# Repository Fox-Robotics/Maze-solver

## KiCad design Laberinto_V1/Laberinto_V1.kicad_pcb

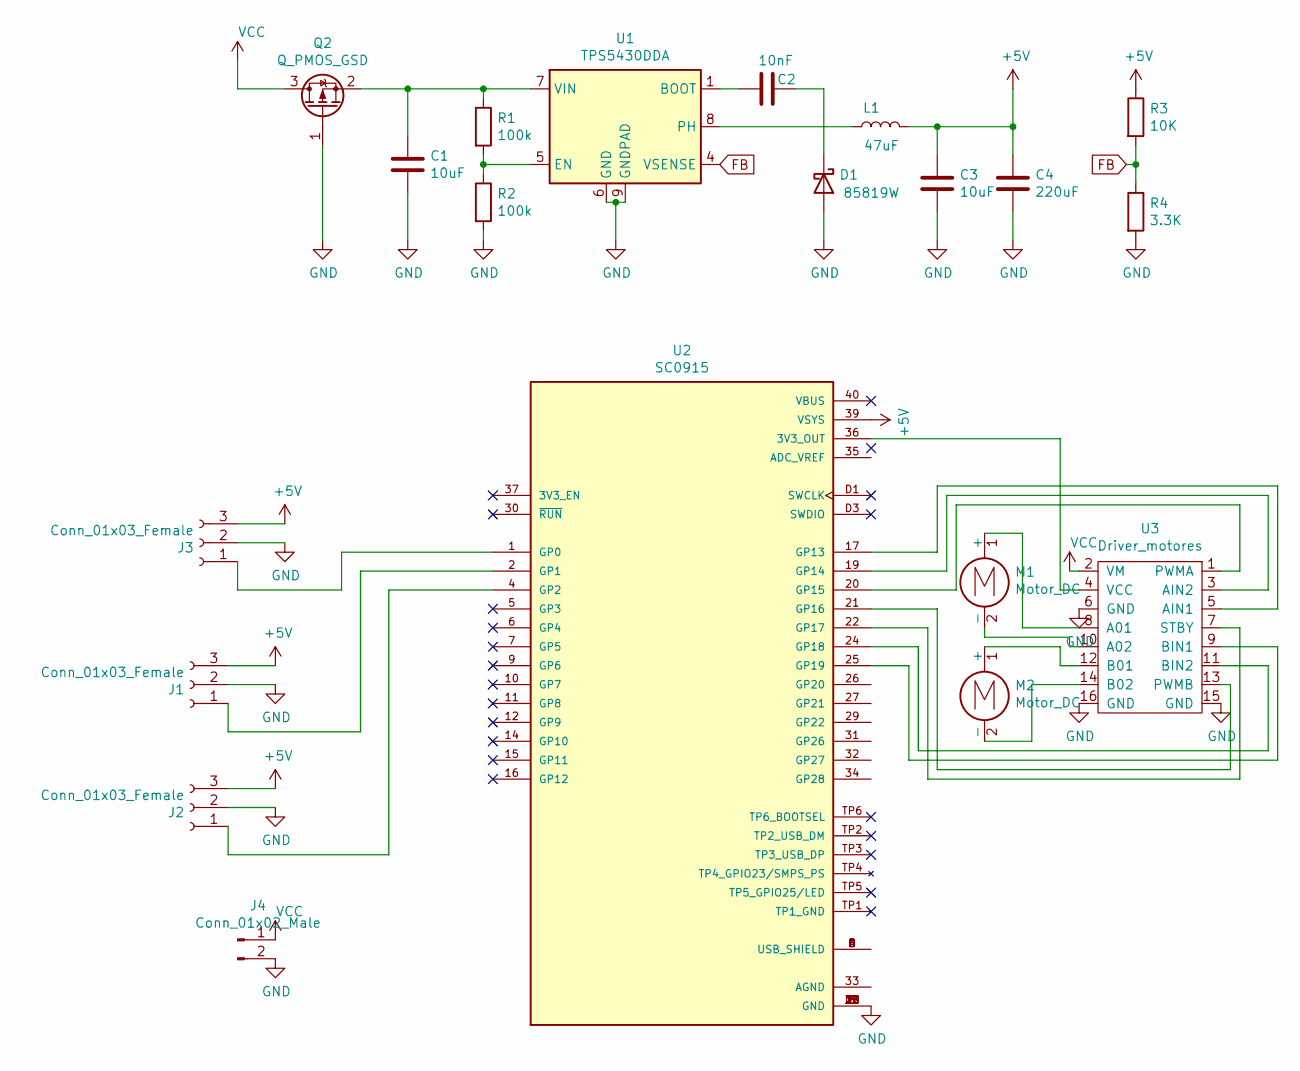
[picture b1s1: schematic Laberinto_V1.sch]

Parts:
C1: 10uF; CP_Elec_5x5.9
C2: 10nF; C_0805_2012Metric_Pad1.18x1.45mm_HandSolder
C3: 10uF; C_0805_2012Metric_Pad1.18x1.45mm_HandSolder
C4: 220uF; CAP_10TPB220M
D1: 85819W; D_SOD-123F
J1, J2, J3: Conn_01x03_Female; PinSocket_1x03_P2.54mm_Horizontal
J4: Conn_01x02_Male; PinHeader_1x02_P2.54mm_Vertical
L1: 47uF; L_0805_2012Metric_Pad1.15x1.40mm_HandSolder
M1, M2: Motor_DC; PinHeader_1x02_P2.54mm_Vertical
Q2: Q_PMOS_GSD; SOT23
R1, R2: 100k; R_0805_2012Metric_Pad1.20x1.40mm_HandSolder
R3: 10K; R_0805_2012Metric_Pad1.20x1.40mm_HandSolder
R4: 3.3K; R_0805_2012Metric_Pad1.20x1.40mm_HandSolder
U1: TPS5430DDA; TI_SO-PowerPAD-8_ThermalVias
U2: SC0915; MODULE_SC0915; PARTREV 1.6
U3: Driver_motores; Motor_driver

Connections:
+5V: C3.1, C4.1, J1.3, J2.3, J3.3, L1.2, R3.1, U2.39 (VSYS)
FB: R3.2, R4.1, U1.4 (VSENSE)
GND: C1.2, C3.2, C4.2, D1.2 (A), J1.2, J2.2, J3.2, J4.2, Q2.1 (G), R2.2, R4.2, U1.6 (GND), U1.9 (GNDPAD), U2.3 (GND), U2.8 (GND), U2.13 (GND), U2.18 (GND), U2.23 (GND), U2.28 (GND), U2.38 (GND), U2.D2 (GND), U3.6 (GND), U3.15 (GND), U3.16 (GND)
unnamed: C1.1, Q2.2 (S), R1.1, U1.7 (VIN)
unnamed: C2.1, D1.1 (K)
unnamed: C2.2, U1.1 (BOOT)
unnamed: J1.1, U2.2 (GP1)
unnamed: J2.1, U2.4 (GP2)
unnamed: J3.1, U2.1 (GP0)
unnamed: L1.1, U1.8 (PH)
unnamed: M1.1 (+), U3.8 (A01)
unnamed: M1.2 (-), U3.10 (A02)
unnamed: M2.1 (+), U3.12 (B01)
unnamed: M2.2 (-), U3.14 (B02)
unnamed: R1.2, R2.1, U1.5 (EN)
unnamed: U2.17 (GP13), U3.5 (AIN1)
unnamed: U2.19 (GP14), U3.3 (AIN2)
unnamed: U2.20 (GP15), U3.1 (PWMA)
unnamed: U2.21 (GP16), U3.13 (PWMB)
unnamed: U2.22 (GP17), U3.7 (STBY)
unnamed: U2.24 (GP18), U3.11 (BIN2)
unnamed: U2.25 (GP19), U3.9 (BIN1)
unnamed: U2.36 (3V3_OUT), U3.4 (VCC)
unnamed: U2.A (USB_SHIELD), U2.B (USB_SHIELD), U2.C (USB_SHIELD), U2.D (USB_SHIELD)
VCC: J4.1, Q2.3 (D), U3.2 (VM)

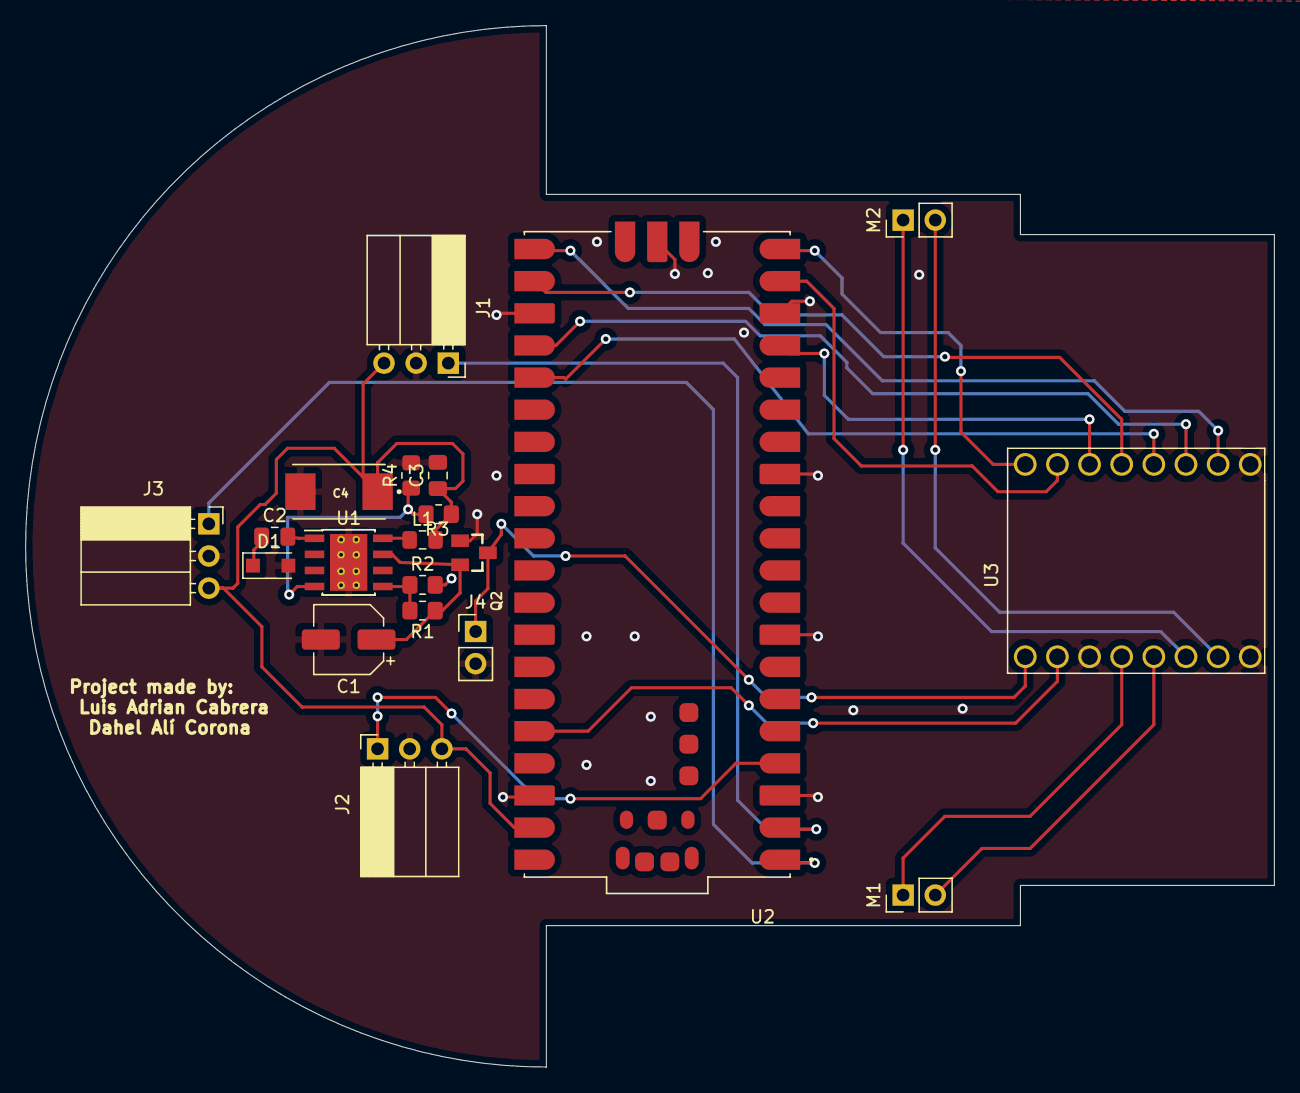
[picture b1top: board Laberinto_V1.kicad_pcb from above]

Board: 2 copper layers, 98.7 x 82.3 mm, 20 parts (0 on the bottom side), 25 nets.

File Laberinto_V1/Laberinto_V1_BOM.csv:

"Id";"Designator";"Package";"Quantity";"Designation";"Supplier and ref";
1;"R3";"R_0805_2012Metric_Pad1.20x1.40mm_HandSolder";1;"10K";;;
2;"C1";"CP_Elec_5x5.9";1;"10uF";;;
3;"C4";"CAP_10TPB220M";1;"220uF";;;
4;"D1";"D_SOD-123F";1;"85819W";;;
5;"J1,J2,J3";"PinSocket_1x03_P2.54mm_Horizontal";3;"Conn_01x03_Female";;;
6;"L1";"L_0805_2012Metric_Pad1.15x1.40mm_HandSolder";1;"47uF";;;
7;"R1,R2";"R_0805_2012Metric_Pad1.20x1.40mm_HandSolder";2;"100k";;;
8;"R4";"R_0805_2012Metric_Pad1.20x1.40mm_HandSolder";1;"3.3K";;;
9;"U1";"TI_SO-PowerPAD-8_ThermalVias";1;"TPS5430DDA";;;
10;"U2";"MODULE_SC0915";1;"SC0915";;;
11;"C2";"C_0805_2012Metric_Pad1.18x1.45mm_HandSolder";1;"10nF";;;
12;"C3";"C_0805_2012Metric_Pad1.18x1.45mm_HandSolder";1;"10uF";;;
13;"U3";"Motor_driver";1;"Driver_motores";;;
14;"M1,M2";"PinHeader_1x02_P2.54mm_Vertical";2;"Motor_DC";;;
15;"J4";"PinHeader_1x02_P2.54mm_Vertical";1;"Conn_01x02_Male";;;
16;"Q2";"SOT23";1;"Q_PMOS_GSD";;;
